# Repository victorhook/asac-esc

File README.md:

# asac esc

**A** **S**imple **A**nd **C**ool **E**lectronic **S**peed **C**ontroller (asac esc) is an open source ESC, including both hardware and software. The firmware is written in pure C.

## PCB Rev. A

First iteration of PCB is done. All cad files can be found in [kicad/asac-esc-rev-a](kicad/asac-esc-rev-a) and the schematic as PDF can be found there, or in [docs/asac-esc-rev-a.pdf](docs/asac-esc-rev-a.pdf).

## Workings of asac esc

Driving a brushless DC (bldc) motor is done by energizing one of the coils at the time which creates a magnetic field that makes the rotor move due to the magnets on it. Making the rotor move "1 step" is referred to as one *commutation* and making a bldc motor spin is not more complicated than energizing the different coils of the stator repeatedly. How fast a commutation takes will dictate how fast the motor will spin, thus controlling the speed of a bldc motor is done by controlling the speed of the commutations. This is accomplished by driving higher or lower amounts of current through the coils, which creates stronger or weaker magnetic fields, which in turn means that the commutation will be faster or slower.

#### Stator and rotor

#### 6-step commutation

Most (perhaps all?) bldc motors has more than 3 coils, but some of the coils are wired together, so that we get only *three* wires out of the motor. We can call each of these wires a *phase*, A, B and C. The commutation sequence consists of 6 unique steps, which then repeats. During each of the 6 steps, one specific phase will get current running into it, and one phase will have current running out of it. Letting current into and out of a phase can be accomplished with the help of mosfets in half-bridge configurations, whereas it's needed with one half-bridge per phase, which means 6 mosfets in total. This way of driving a bldc is motor is referred to as *6-step commutation*.

There are penty of good resources online that describes this process in much detail, such as [here](https://www.digikey.com/en/articles/how-to-power-and-control-brushless-dc-motors).

This image describes the 6 different states. It's slightly simplified, since a "1" doesn't really mean a logic high, nor 1 volt, but simply means that the phase allows current into it, whereas a "0" means that current runs out of the phase. The mosfets are not actually driven by 1s and 0s, but controlled using PWM, which is described in more detail below. The "Z" means that the phase is floating.

Below is an example os the first 2 steps, whereas current runs into phase A and out of phase B, and then out of phase C in step 2.

Commutation state 1 - Current flows into phase **A** and out of **B**.

Commutation state 2 - Current flows into phase **A** and out of **C**.

And so forth for the steps 4-6...

#### BEMF closed-loop control

While it's possible to run a bldc motor *without* any feedback, it's only going to work at a constrained speed, since we have no indication of where the rotor is. If the position of the rotor is unknown, it's impossible to know exactly *when* to turn on a specific phase, and knowing *when* to do the next commutation can be accomplished by inspecting the back electromotive (bemf) force that is induced in the third ("unused") floating phase. In the schematic above you can see that each phase has a "VSENSE_X" connected to it through a voltage divider. This will be connected to an ADC on the microcontroller.

The bemf will follow (roughly) the pattern as described in the image below:

Let's say that we're in step 3, where phase A have just been turned off and left floating. The voltage of the phase is still high, but will after some time go back to zero. The trick here is that we want to detect the middle point of this slope in order to schedule the next commutation. This "middle point" is referred to as *zero cross*. Note that the zero cross is not actually at 0, but the middle point between the highest voltage and zero, thus `zero_cross = vmax / 2`. For this to work we must know which commutation state we're in, since the slope of the bemf-values changes for each state (up/down). The bemf adc value is sampled on each update loop in order to detect when the bemf value crosses the zero cross.

Using bemf as input to know when to switch commutation step is referred to as running in *closed-loop*.

So how do we accomplish this in code? The mosfets that are connected to the high side of the half-bridges are turned on to allow current through, and the mosfets on the low side are driven low to allow current flow through them to ground. Note that the high-side mosfets are driven with a PWM signal which makes it possible to control how much current should flow through the coils. What frequency the PWM signal should have depends on the motor, but asac esc runs PWM on a frequency of 24 kHz (23437.5 Hz) with a duty resolution of 2048. Higher PWM will mean more current -> stronger magnetic field -> faster commutation.

Once a zero cross has been detected, the next commutation is scheduled to be performed in about half a commutation period from the detection. This commutation period time duration is taken from the last commutation period. Note that some delays such as update loop and filtering is subtracted, so in reality the next commutation is scheduled to be something like:
```
if (zero_cross_detected)
{
    next_commutation = now + half_commutation_period - filter_delay - update_delay
}
```

#### Start-up phase
An issue with using back-emf to know when to switch to the next commutation state is that before the motor is spinning we have no knowledge of where the rotor is. A solution to this problem is to start spinning the motor in *open-loop* mode, which means that the commutation states are traversed with a *fixed* period. During this time, the back-emf is still being looked at, to detect when we can switch to closed-loop. This is done if a zero-cross is detected, that seems to come in a "reasonable" time. By "reasonable" time, I mean that its detected roughly in the middle of a commutation period.

#### Input signal
asac esc supports standard input signals such as:
- 50 Hz (1000-2000 us)

These are all in the form of a pulse, whereas the pulse length is directly proportional to the throttle value.

The pulses are detected by an interrupt on the pin.

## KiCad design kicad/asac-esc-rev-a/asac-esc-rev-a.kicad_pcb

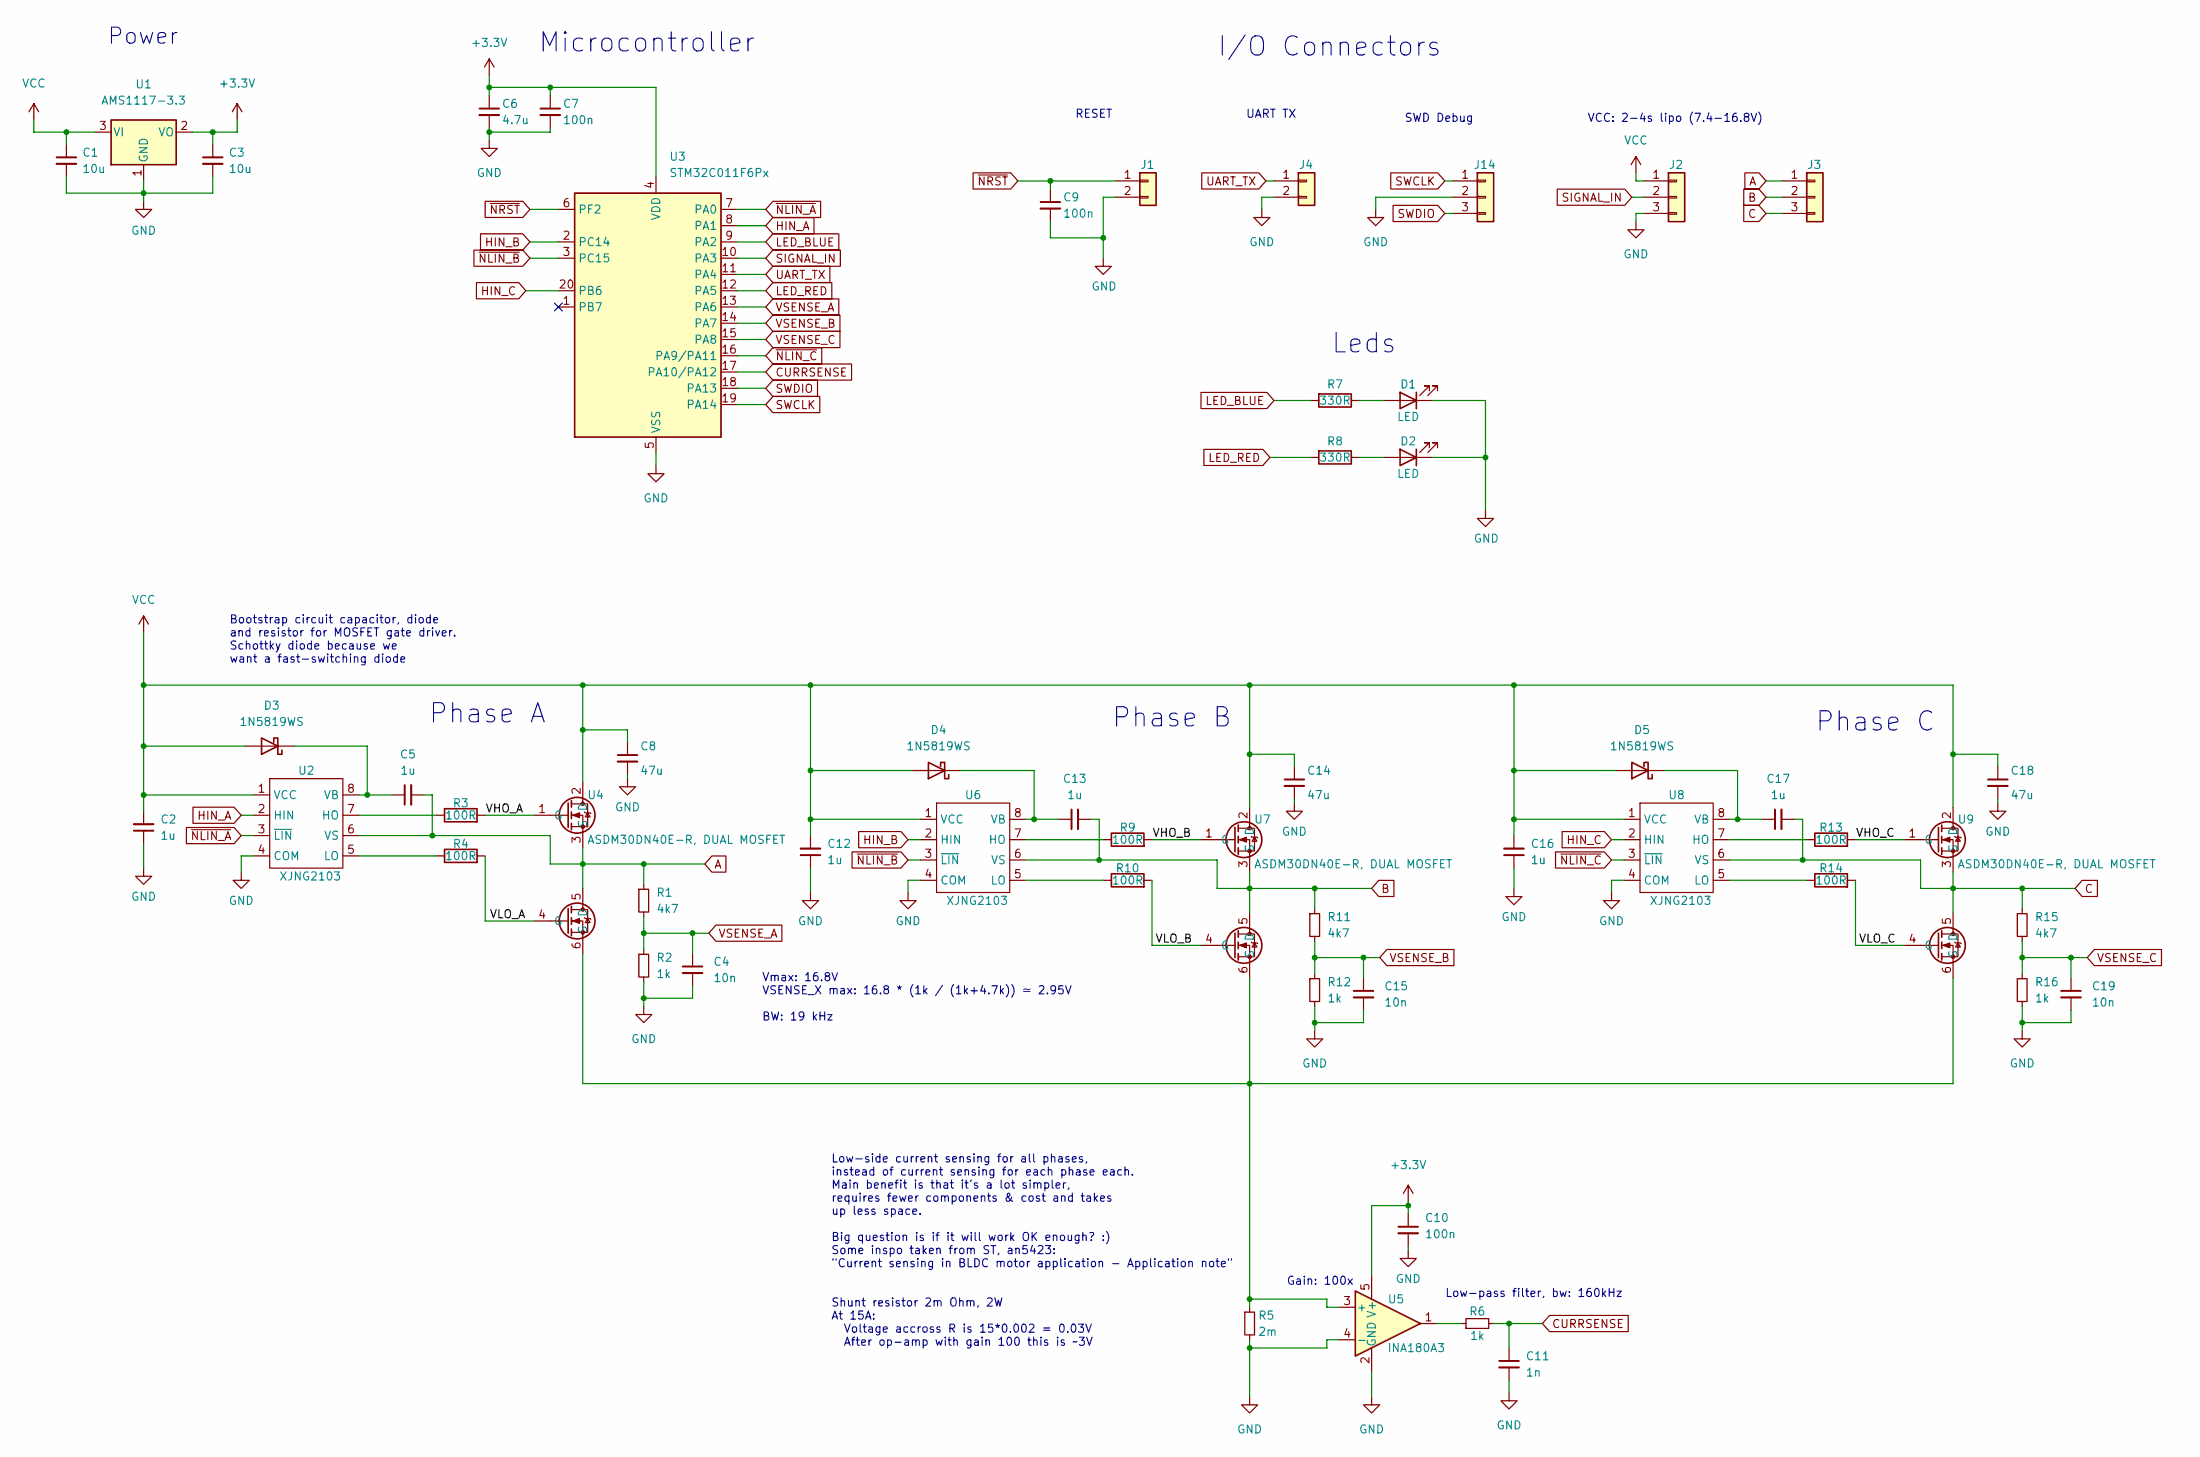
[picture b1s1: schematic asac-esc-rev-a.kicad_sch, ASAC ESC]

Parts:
C1, C3: 10u; C_0805_2012Metric
C2, C5, C12, C13, C16, C17: 1u; C_0402_1005Metric
C4, C15, C19: 10n; C_0402_1005Metric
C6: 4.7u; C_0603_1608Metric
C7, C9, C10: 100n; C_0402_1005Metric
C8, C14, C18: 47u; C_1206_3216Metric
C11: 1n; C_0402_1005Metric
D1, D2: LED; LED_0603_no_outline
D3, D4, D5: 1N5819WS; D_SOD-323
J1, J4: Conn_01x02_RESET; PinHeader_1x02_P2.54mm_Vertical_No_silk
J2: Conn_01x03; Conn_01x03_BLDC
J3: Motor; Conn_01x03_BLDC
J14: Conn_01x03; PinSocket_1x03_P2.54mm_Vertical_No_silk
R1, R11, R15: 4k7; R_0402_1005Metric
R2, R6, R12, R16: 1k; R_0402_1005Metric
R3, R4, R9, R10, R13, R14: 100R; R_0603_1608Metric
R5: 2m; R_2512_6332Metric
R7, R8: 330R; R_0402_1005Metric
U1: AMS1117-3.3; SOT-223-3_TabPin2
U2, U6, U8: XJNG2103; SOIC-8_3.9x4.9mm_P1.27mm
U3: STM32C011F6Px; TSSOP-20_4.4x6.5mm_P0.65mm
U4, U7, U9: ASDM30DN40E-R, DUAL MOSFET; PDFN3333-8_L3.2-W3.1-P0.65-LS3.4-BL
U5: INA180A3; SOT-23-5

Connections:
+3.3V: C3.1, C6.1, C7.1, C10.1, U1.2 (VO), U3.4 (VDD), U5.5 (V+)
/VHO_A: R3.2, U4.1 (G)
/VHO_B: R9.2, U7.1 (G)
/VHO_C: R13.2, U9.1 (G)
/VLO_A: R4.2, U4.4 (G)
/VLO_B: R10.2, U7.4 (G)
/VLO_C: R14.2, U9.4 (G)
A: C5.2, J3.1, R1.1, U2.6 (VS), U4.3 (S), U4.5 (D)
B: C13.2, J3.2, R11.1, U6.6 (VS), U7.3 (S), U7.5 (D)
C: C17.2, J3.3, R15.1, U8.6 (VS), U9.3 (S), U9.5 (D)
CURRSENSE: C11.1, R6.2, U3.17 (PA10/PA12)
GND: C1.2, C2.1, C3.2, C4.2, C6.2, C7.2, C8.2, C9.2, C10.2, C11.2, C12.1, C14.2, C15.2, C16.1, C18.2, C19.2, D1.1 (K), D2.1 (K), J1.2, J2.3, J4.2, J14.2, R2.2, R5.2, R12.2, R16.2, U1.1 (GND), U2.4 (COM), U3.5 (VSS), U5.2 (GND), U5.4 (-), U6.4 (COM), U8.4 (COM)
HIN_A: U2.2 (HIN), U3.8 (PA1)
HIN_B: U3.2 (PC14), U6.2 (HIN)
HIN_C: U3.20 (PB6), U8.2 (HIN)
LED_BLUE: R7.2, U3.9 (PA2)
LED_RED: R8.2, U3.12 (PA5)
unnamed: C5.1, D3.1 (K), U2.8 (VB)
unnamed: C13.1, D4.1 (K), U6.8 (VB)
unnamed: C17.1, D5.1 (K), U8.8 (VB)
unnamed: D1.2 (A), R7.1
unnamed: D2.2 (A), R8.1
unnamed: R3.1, U2.7 (HO)
unnamed: R4.1, U2.5 (LO)
unnamed: R5.1, U4.6 (S), U5.3 (+), U7.6 (S), U9.6 (S)
unnamed: R6.1, U5.1
unnamed: R9.1, U6.7 (HO)
unnamed: R10.1, U6.5 (LO)
unnamed: R13.1, U8.7 (HO)
unnamed: R14.1, U8.5 (LO)
SIGNAL_IN: J2.2, U3.10 (PA3)
SWCLK: J14.1, U3.19 (PA14)
SWDIO: J14.3, U3.18 (PA13)
UART_TX: J4.1, U3.11 (PA4)
VCC: C1.1, C2.2, C8.1, C12.2, C14.1, C16.2, C18.1, D3.2 (A), D4.2 (A), D5.2 (A), J2.1, U1.3 (VI), U2.1 (VCC), U4.2 (D), U6.1 (VCC), U7.2 (D), U8.1 (VCC), U9.2 (D)
VSENSE_A: C4.1, R1.2, R2.1, U3.13 (PA6)
VSENSE_B: C15.1, R11.2, R12.1, U3.14 (PA7)
VSENSE_C: C19.1, R15.2, R16.1, U3.15 (PA8)
~NLIN_A: U2.3 (~LIN), U3.7 (PA0)
~NLIN_B: U3.3 (PC15), U6.3 (~LIN)
~NLIN_C: U3.16 (PA9/PA11), U8.3 (~LIN)
~NRST: C9.1, J1.1, U3.6 (PF2)

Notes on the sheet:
Phase C
RESET
Leds
Phase B
Gain: 100x
SWD Debug
Low-pass filter, bw: 160kHz
Phase A
I/O Connectors
VCC: 2-4s lipo (7.4-16.8V)
Vmax: 16.8V VSENSE_X max: 16.8 * (1k / (1k+4.7k)) ≃ 2.95V BW: 19 kHz
Power
Bootstrap circuit capacitor, diode and resistor for MOSFET gate driver. Schottky diode because we want a fast-switching diode
UART TX
Low-side current sensing for all phases, instead of current sensing for each phase each. Main benefit is that it's a lot simpler, requires fewer components & cost and takes up less space. Big question is if it will work OK enough? :) Some inspo taken from ST, an5423: "Current sensing in BLDC motor 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
Microcontroller

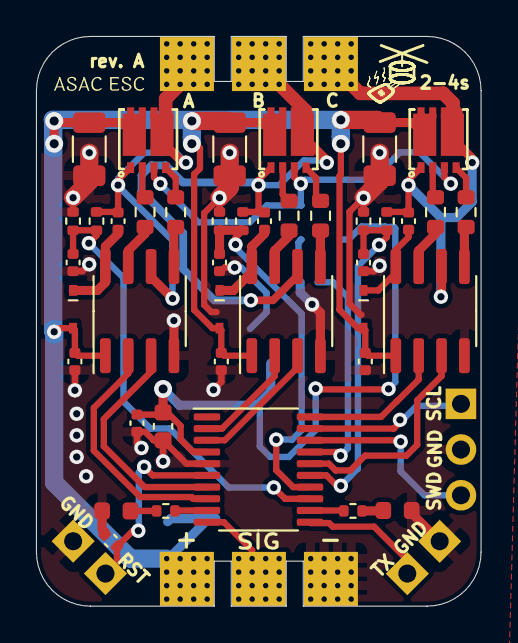
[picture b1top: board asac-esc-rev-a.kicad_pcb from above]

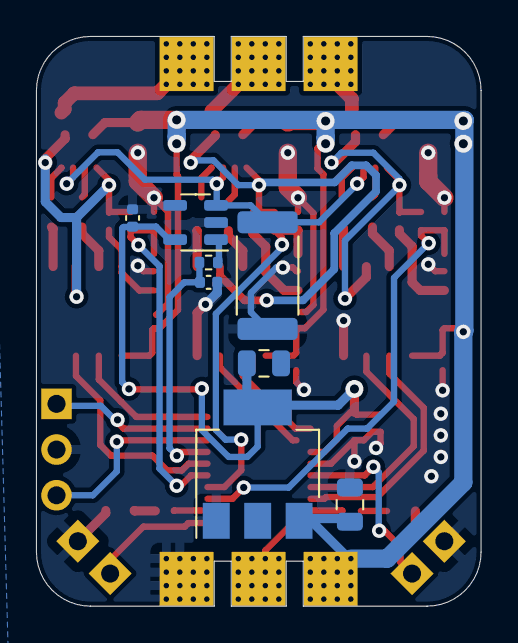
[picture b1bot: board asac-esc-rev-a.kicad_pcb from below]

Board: 2 copper layers, 24.7 x 31.7 mm, 54 parts (8 on the bottom side), 42 nets.

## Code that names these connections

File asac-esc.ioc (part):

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Mcu.Name=STM32C011F(4-6)Px
Mcu.Package=TSSOP20
Mcu.UserName=STM32C011F6Px
PA0.Signal=S_TIM1_CH1
PA1.Signal=S_TIM1_CH2
PA11\ [PA9].Signal=S_TIM1_CH4
PA12\ [PA10].Mode=IN12
PA12\ [PA10].Signal=ADC1_IN12
PA13.Mode=Serial_Wire
PA13.Signal=DEBUG_SWDIO
PA14-BOOT0.Mode=Serial_Wire
PA14-BOOT0.Signal=DEBUG_SWCLK
PA2.Signal=GPIO_Output
PA3.Signal=GPXTI3
PA5.Signal=GPIO_Output
PA6.Mode=IN6
PA6.Signal=ADC1_IN6
PA7.Mode=IN7
PA7.Signal=ADC1_IN7
PA8.Mode=IN8
PA8.Signal=ADC1_IN8
PB6.Signal=S_TIM1_CH3
PC14-OSCX_IN\ (PC14).Signal=S_TIM3_CH2
PC15-OSCX_OUT\ (PC15).Signal=S_TIM3_CH3
RCC.HSE_VALUE=8000000
RCC.SYSCLKFreq_VALUE=12000000
board=custom

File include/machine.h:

#ifndef MACHINE_H
#define MACHINE_H

#define PIN_LED_RED GPIO_PIN_5
#define PORT_LED_RED GPIOA
#define PIN_LED_BLUE GPIO_PIN_2
#define PORT_LED_BLUE GPIOA

// A
#define PIN_HIN_A  GPIO_PIN_1
#define PIN_LIN_A  GPIO_PIN_0
#define PORT_HIN_A GPIOA
#define PORT_LIN_A GPIOA
// B
#define PIN_HIN_B  GPIO_PIN_14
#define PIN_LIN_B  GPIO_PIN_15
#define PORT_HIN_B GPIOC
#define PORT_LIN_B GPIOC
// C
#define PIN_HIN_C  GPIO_PIN_6
#define PIN_LIN_C  GPIO_PIN_11
#define PORT_HIN_C GPIOB
#define PORT_LIN_C GPIOA

#define ADC_CHANNEL_PHASE_A ADC_CHANNEL_6
#define ADC_CHANNEL_PHASE_B ADC_CHANNEL_7
#define ADC_CHANNEL_PHASE_C ADC_CHANNEL_8

//#define ADC_CHANNEL_PHASE_A ADC_CHSELR_CHSEL6
//#define ADC_CHANNEL_PHASE_B ADC_CHSELR_CHSEL7
//#define ADC_CHANNEL_PHASE_C ADC_CHSELR_CHSEL8

#endif /* MACHINE_H */

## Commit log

2023-06-11 Created separate sheet for phase A, almost done with it.
2023-06-12 Decided on microcontroller: STM32C011F6P6. The reason for this mcu is that it's quite new, quite cheap, is available on LCSC is developed and maintained by STM. The mcu should have just enough pins f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
2023-06-13 Changed from current sensing each phase to a single current sensing circuit for all MOSFETs. Primary motivation is that it's simpler, let's just hope that it works OK...!
    Pretty much done with schematic now, everything is not
    connected to the MCU yet however, since the layout might
    have an impact on exactly which port should be connected
    where.
2023-06-16 Did layout and routing of PCB. Rev. A of the PCB is considered done and I have just done the order for PCB and components :)
2023-07-05 Rev. A Done and arrived, time to solder!
2023-07-06 Firmware project setup
    - Created project in STM32CubeMX
    - Created initial blink sequence in main.c
    - Created json launch file for debugging
    - Added flash-target in makefile to flash
2023-07-15 First test done, managed to spin motor!
    - Moved HAL inits to separate file (hal.c
    for now). Should make a different
    solution for this in the future, but I'd
    like to not follow the CubeMX project
    structure since I don't think it's too
    intuitive.
2023-07-16 Added initial closed-loop control
    - Added ADC handling that reads the
    BEMF from each phase when the
    phase is not active.
    - Made the startup from 0 throttle ->
    to something start with open-loop
    control, whereas it goes over to closed-
2023-07-17 Got closed-loop control to work OK, but the logic is somewhat wrong, since the commutation happens at the zero-cross detection, which it should not be. It should happen half a commutation AFTER..?
2023-07-18 Closed-loop zero detection
    - Added simple check for the zero-cross-detection in closed-loop mode.
    The goal is to have the transition from closed-loop to open-loop smother and
    look for the bemf zero-cross in order to switch mode.
    - Some refactorization, moved most variables to state_t.
2023-07-18 Added images of PCB and updated README
2023-07-19 Refactored some functions and files
2023-07-19 LED pin bugfix and open-loop improvement
2023-07-22 Refactor and cleanup
    - Put timer 14 (micros()/millis() timer) update logic into a separate
    method, separate from man update function.
    - Made separate method for switching to open loop
    - Some cleanup of variable declarations (eg now, zero_cross_detected)
2023-07-22 Audio support and new mode
    - Added ability to play tones with the motors, as well as melodies.
    - Added new mode (MODE_ARMING_SEQUENCE_STARTED) similar to blheli,
    so so that we require a throttle value of 0 in order to arm.
    - Added support for changing direction to reversed.
    - Added sleep functions, sleep_us and sleep_ms
2023-07-24 Added a lot of info and documentation of workings of asac esc
2023-07-25 Refactoring
    - Moved audio methods and definitions to separate module
    - Change audio to consume less power
    - Added oneshot detection, needs to be tested though
    - Turned off/on interrupts on pulse ISR.
    Note sure if this makes any difference..
